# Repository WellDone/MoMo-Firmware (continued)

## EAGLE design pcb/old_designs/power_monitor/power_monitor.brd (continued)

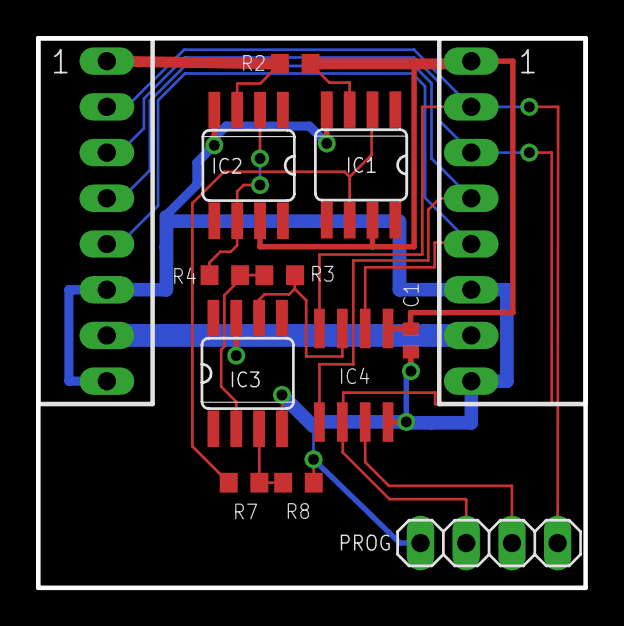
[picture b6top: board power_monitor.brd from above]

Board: 2 copper layers, 30.4 x 30.5 mm, 13 parts (0 on the bottom side), 14 nets.

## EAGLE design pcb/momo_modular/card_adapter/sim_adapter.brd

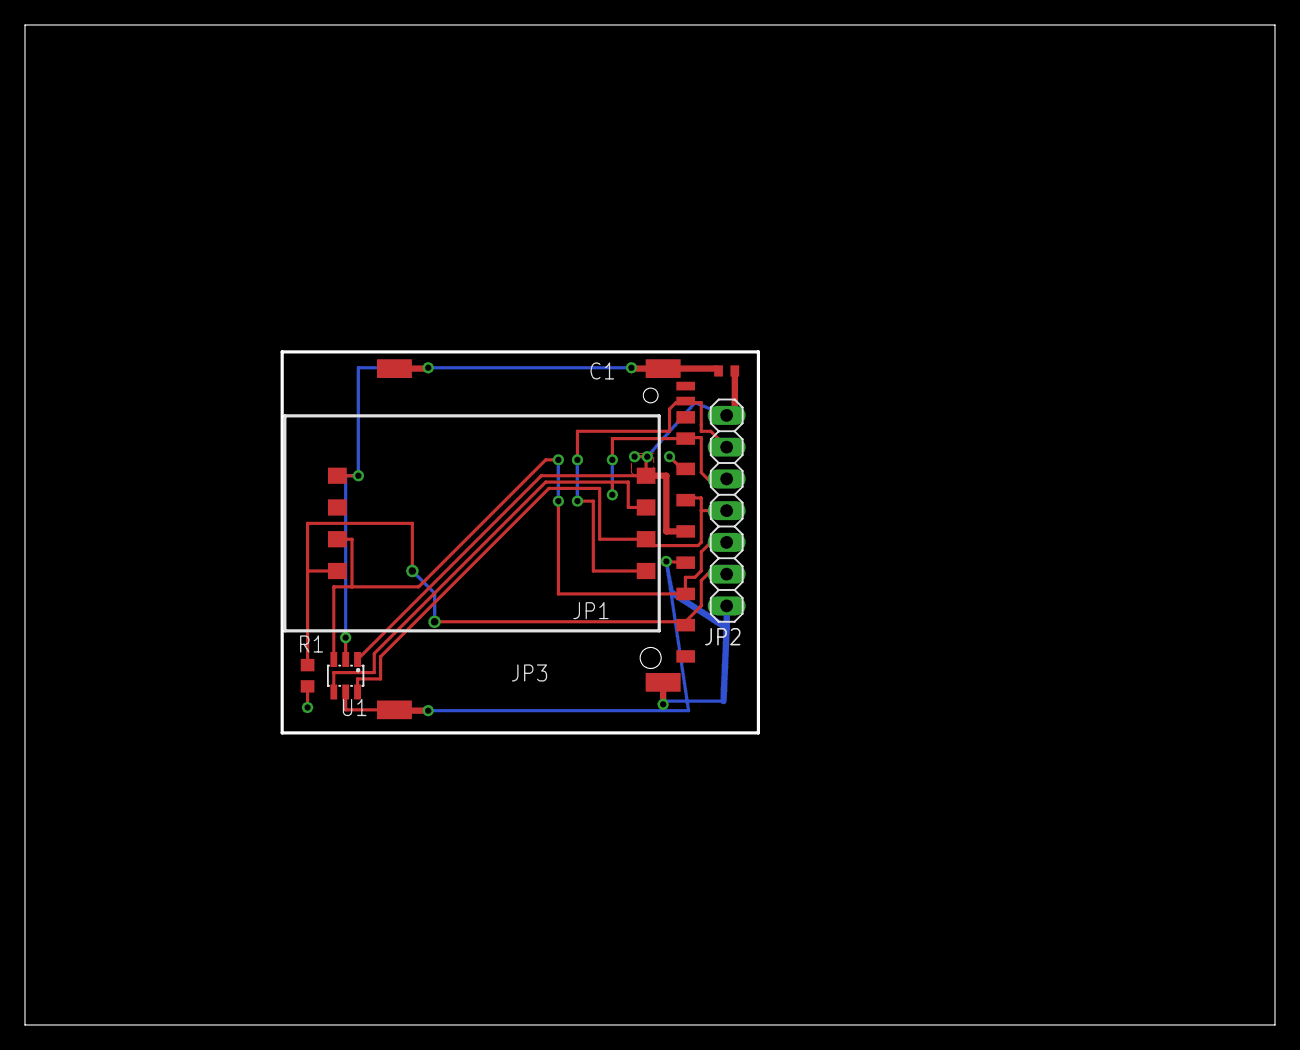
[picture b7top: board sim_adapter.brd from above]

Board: 2 copper layers, 99.7 x 79.7 mm, 6 parts (0 on the bottom side), 7 nets.

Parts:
C1: 100 nF; C0402
JP1: SIMHOLDER-8PINHING; CCM03-SIMHOLDER
JP2: 1X07
JP3: SDCARD-HOLDER; SDHOLDER-9PIN
R1: 10K; R0603
U1: ESDA6V1SC6; SOT23-6L

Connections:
GND: C1.2, JP1.GND, JP2.1, JP3.3, JP3.6, JP3.CDGND, JP3.CDGND_BOT, JP3.WPGND, JP3.WPGND_BOT, R1.2, U1.2, U1.5
IO1: JP1.SW2, JP2.2, JP3.1, R1.1
IO2: JP1.IO, JP2.3, JP3.2, U1.3
IO3: JP1.RESET, JP2.5, JP3.7, U1.4
IO4: JP1.CLOCK, JP2.4, JP3.5, U1.6
SENSE: JP1.SW1, JP2.6, JP3.CDETECT
VCC: C1.1, JP1.VCC, JP2.7, JP3.4, U1.1

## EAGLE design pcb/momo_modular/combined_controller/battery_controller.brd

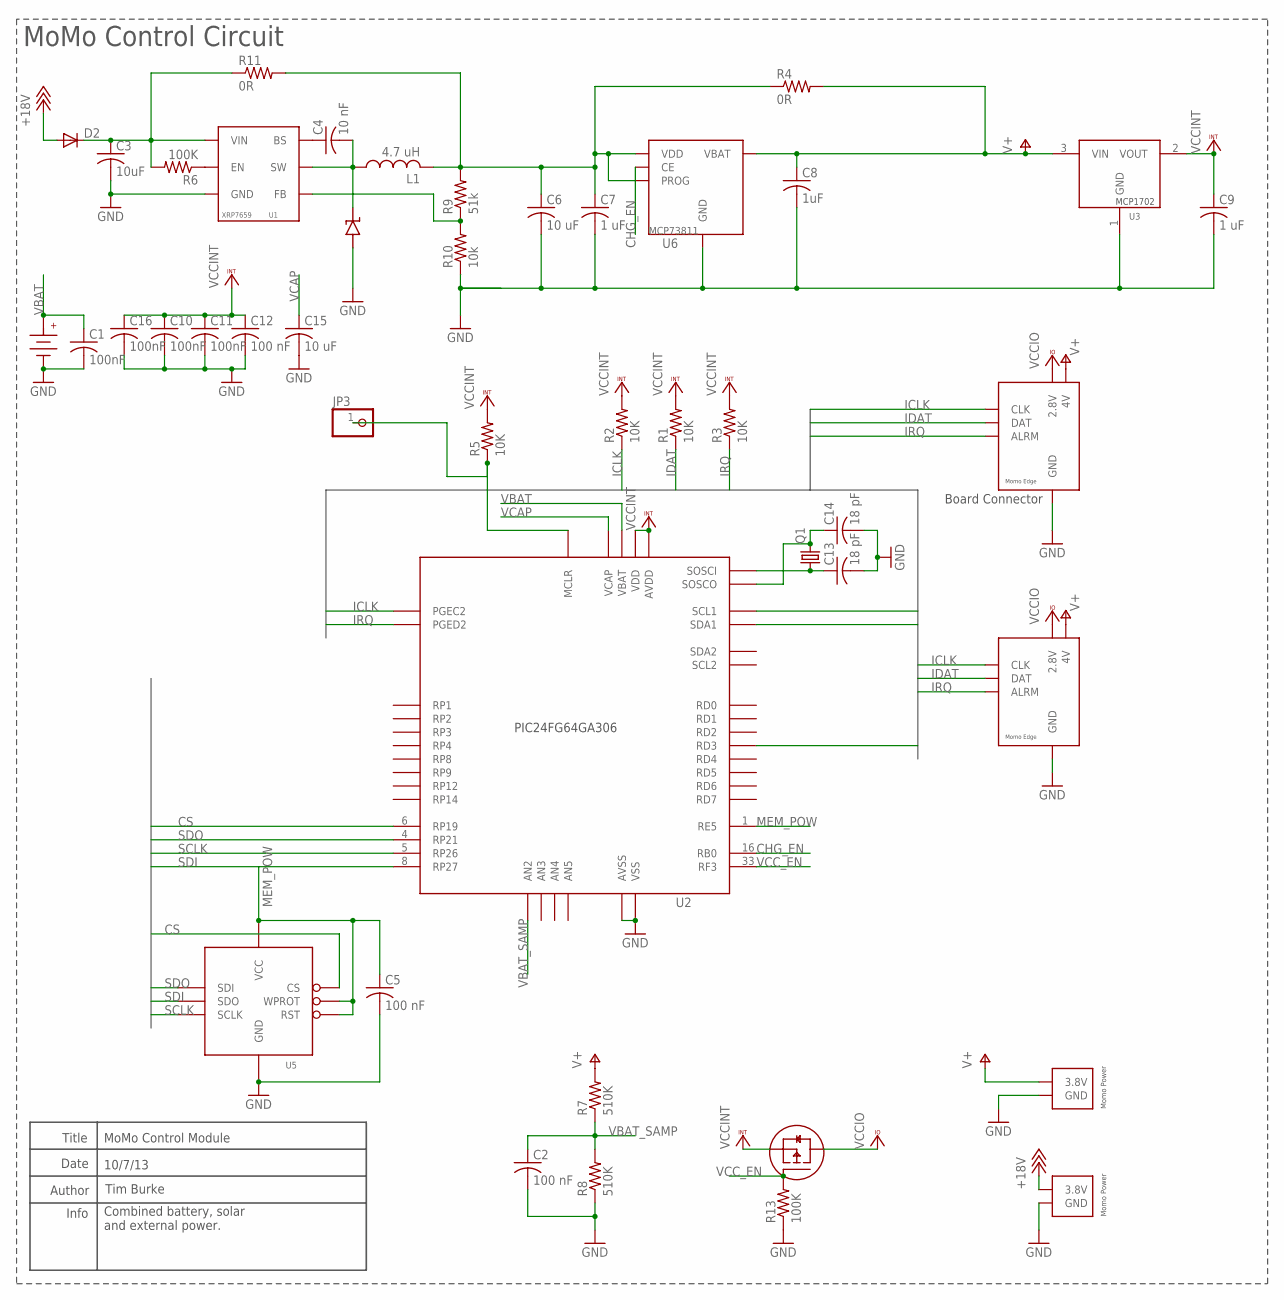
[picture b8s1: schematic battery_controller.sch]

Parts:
BATT1: CR1025-HOLDER
C1, C10, C11, C16: 100nF; C0402; DIGIKEY-PN 445-1265-1-ND
C2, C5, C12: 100 nF; C0402; DIGIKEY-PN 445-1265-1-ND
C3: 10uF; C0805; DIGIKEY-PN-BATT 587-2985-1-ND
C4: 10 nF; C0402; DIGIKEY-PN-BATT 445-1260-1-ND
C6: 10 uF; C0805; DIGIKEY-PN-BATT 587-2985-1-ND
C7: 1 uF; C0402; DIGIKEY-PN-BATT 445-4114-1-ND
C8: 1uF; C0402; DIGIKEY-PN-BATT 445-4114-1-ND
C9: 1 uF; C0402; DIGIKEY-PN 445-4114-1-ND
C13, C14: 18 pF; C0402K; DIGIKEY-PN 445-1238-1-ND
C15: 10 uF; C0805; DIGIKEY-PN 1276-1119-1-ND
D1: DIODE_SS2P3SS2P3; DIODE_SS2P3; DIGIKEY-PN-BATT SS2P3-M3/84AGICT-ND
D2: DIODE-DO214AC; DO214AC; DIGIKEY-PN SL13HE3/61TGICT-ND
JP1: MOMO-VERT-6M; 1X06; DIGIKEY-PN S1011EC-06-ND
JP2: MOMO-EDGE-6F; MOMO-EDGE-8F
JP3: PINHD-1X1; 1X01
JP4, JP5: MOMO-EDGE-POWER-M; MOMO-EDGE-SMALL-2M; DIGIKEY-PN A19450-ND
L1: 4.7 uH; NR6028-INDUCTOR; DIGIKEY-PN-BATT 587-2100-1-ND
Q1: CRYSTALTC26H; TC26H; DIGIKEY-PN 535-9034-ND
Q2: P-MOSFET; SOT23
R1, R2, R3, R5: 10K; R0603; DIGIKEY-PN P10.0KHCT-ND
R4: 0R; R0603; DIGIKEY-PN-EXTPOWER P0.0GCT-ND
R6: 100K; R0603; DIGIKEY-PN-BATT P100KHCT-ND
R7, R8: 510K; R0603; DIGIKEY-PN P510KHCT-ND
R9: 51k; R0603; DIGIKEY-PN-BATT P51.0KHCT-ND
R10: 10k; R0603; DIGIKEY-PN-BATT P10.0KHCT-ND
R11: 0R; R0603; DIGIKEY-PN-SOLAR P0.0GCT-ND
R13: 100K; R0603; DIGIKEY-PN P100KHCT-ND
U1: XRP7659; SOT23-6L; DIGIKEY-PN-BATT 1016-1751-1-ND
U2: PIC24FJ64GA306; TQFP64-10X10
U3: MCP1702; SOT23; DIGIKEY-PN MCP1702T-2802E/CBCT-ND
U5: FLASH8MSOP8; SOP08; DIGIKEY-PN M25PX80-VMN6TPCT-ND
U6: MCP73811; SOT23-5L; DIGIKEY-PN-BATT MCP73811T-420I/OTCT-ND

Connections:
+18V: D2.A, JP5.2 (3.8V)
BUCK_EN: R6.1, U1.4 (EN)
CHG_EN: U2.16 (RB0), U6.1 (CE)
CS: U2.6 (RP19), U5.1 (CS)
GND: BATT1.-1 (-), BATT1.-2 (-), C1.2, C2.2, C3.2, C5.2, C6.2, C7.2, C8.2, C9.2, C10.2, C11.2, C12.2, C13.2, C14.2, C15.2, C16.2, D1.AN, JP1.7 (GND), JP2.GND, JP4.1 (GND), JP5.1 (GND), R8.1, R10.1, R13.1, U1.2 (GND), U2.9 (VSS), U2.20 (AVSS), U2.25 (VSS), U2.41 (VSS), U3.1 (GND), U5.4 (GND), U6.2 (GND)
ICLK: JP1.3 (CLK), JP2.CLK, R2.1, U2.17 (PGEC2), U2.37 (SCL1)
IDAT: JP1.4 (DAT), JP2.DAT, R1.1, U2.36 (SDA1)
IRQ: JP1.5 (ALRM), JP2.ARLM (ALRM), R3.1, U2.18 (PGED2), U2.51 (RD3)
MEM_POW: C5.1, U2.1 (RE5), U5.3 (WPROT), U5.7 (RST), U5.8 (VCC)
unnamed: C3.1, D2.C, R6.2, R11.1, U1.5 (VIN)
unnamed: JP3.1, R5.1, U2.7 (MCLR)
unnamed: C6.1, C7.1, L1.2, R4.1, R9.2, R11.2, U6.4 (VDD), U6.5 (PROG)
unnamed: C14.1, Q1.2, U2.48 (SOSCO)
unnamed: C13.1, Q1.1, U2.47 (SOSCI)
unnamed: R9.1, R10.2, U1.3 (FB)
unnamed: C4.1, U1.1 (BS)
unnamed: C4.2, D1.CATH, L1.1, U1.6 (SW)
SCLK: U2.5 (RP26), U5.6 (SCLK)
SDI: U2.8 (RP27), U5.2 (SDO)
SDO: U2.4 (RP21), U5.5 (SDI)
V+: C8.1, JP1.6 (4V), JP2.V4 (4V), JP4.2 (3.8V), R4.2, R7.2, U3.3 (VIN), U6.3 (VBAT)
VBAT: BATT1.+, C1.1, U2.57 (VBAT)
VBAT_SAMP: C2.1, R7.1, R8.2, U2.14 (AN2)
VCAP: C15.1, U2.56 (VCAP)
VCCINT: C9.1, C10.1, C11.1, C12.1, C16.1, Q2.2 (SOURCE), R1.2, R2.2, R3.2, R5.2, U2.10 (VDD), U2.19 (AVDD), U2.26 (VDD), U2.38 (VDD), U3.2 (VOUT)
VCCIO: JP1.1 (2.8V), JP2.V28 (2.8V), Q2.3 (DRAIN)
VCC_EN: Q2.1 (GATE), R13.2, U2.33 (RF3)

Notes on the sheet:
Title
Author
Date
Tim Burke
Info
Board Connector
MoMo Control Module
10/7/13
MoMo Control Circuit
Combined battery, solar and external power.

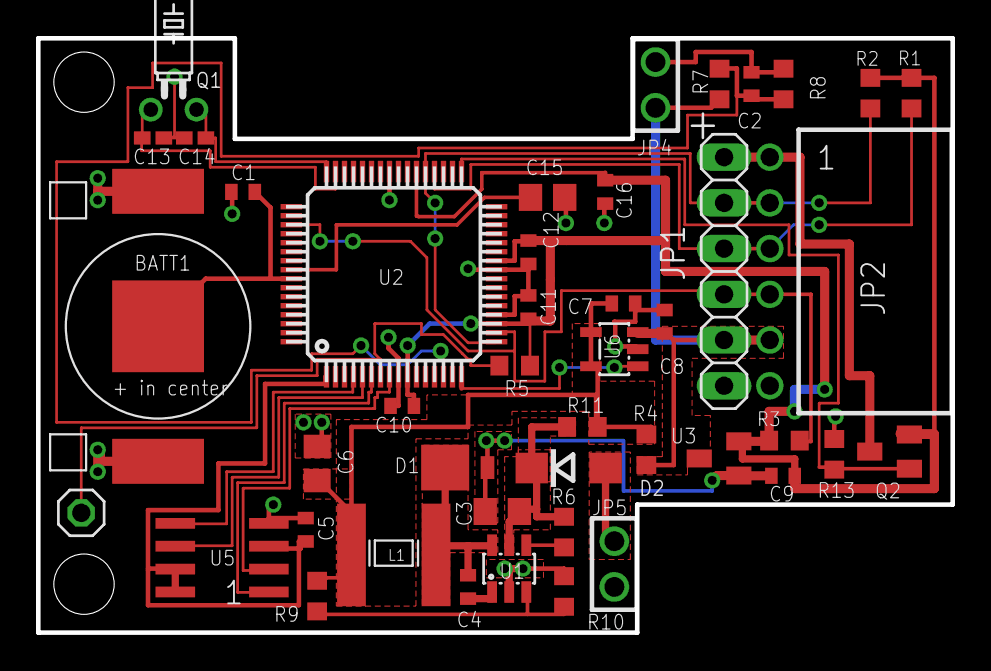
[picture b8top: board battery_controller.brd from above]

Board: 2 copper layers, 50.8 x 33.0 mm, 44 parts (0 on the bottom side), 27 nets.

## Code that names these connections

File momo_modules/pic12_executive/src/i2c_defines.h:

//i2c_defines.h
/*
 * All i2c constant values for sharing between c and asm code.
 */

#ifndef __i2c_defines_h__
#define __i2c_defines_h__

#ifdef __PIC16LF1823__
#define SDAPIN		RC1	
#define SCLPIN		RC0

#define I2CPORT		PORTC

#define SDATRIS		TRISC1
#define SCLTRIS		TRISC0
#define ALARM		A2
#define ALARMIOC	2
#define ALARMPORT	a
#define ALARMPORT_ASM A

#elif  __PIC12LF1822__
#define SDAPIN		RA2	
#define SCLPIN		RA1

#define I2CPORT		PORTA

#define SDATRIS		TRISA2
#define SCLTRIS		TRISA1
#define ALARM		A5
#define ALARMIOC	5
#define ALARMPORT	a
#define ALARMPORT_ASM A

#elif  __PIC16LF1847__
#define SDAPIN		RB1
#define SCLPIN		RB4

#define I2CPORT		PORTB

#define SDATRIS 	TRISB1
#define SCLTRIS		TRISB4
#define ALARM		B0
#define ALARMIOC	0
#define ALARMPORT 	b
#define ALARMPORT_ASM B
#else
#error Unsupported Platform, need to know i2c pin locations.
#endif

#define kI2CIdleState 				0
#define kI2CSendAddressState 		1
#define kI2CSendDataState 			2
#define kI2CReceiveDataState 		3
#define kI2CUserCallbackState 		4

#define kI2CStateMask				0b111
#define kI2CStatusMask				~(kI2cStateMask)
#define kI2CErrorMask				(0b11 << 6)

#define kI2CNoError 				(0 << 6)
#define kI2CInvalidChecksum 		(1 << 6)
#define kI2CNackReceived 			(2 << 6)
#define kI2CCollision 				(3 << 6)

#define kDisableI2CSlewControlFlag 	(1 << 7)
#define kSMBusLevelCompliantFlag 	(1 << 6)

#define kI2CFlagMask (kDisableI2CSlewControlFlag | kSMBusLevelCompliantFlag)

//both set CKP and SSPEN
#define kI2CMasterMode 				0b00111000            //set to master mode (0b1000)
#define kI2CSlaveMode 		        0b00110110            //set to slave mode (0b0110)


#endif

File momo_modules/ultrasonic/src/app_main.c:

//app_main.c

#include "platform.h"
#include "watchdog.h"
#include "port.h"
#include "mib12_api.h"
#include "watchdog.h"
#include "ioc.h"
#include "wpu.h"
#include "communication.h"
#include "tdc1000.h"
#include "tdc7200.h"
#include "measure.h"
#include "state.h"
#include "autoconf.h"
#include "automeasure.h"
#include <stdint.h>

//Global State
module_state	state;

static void copy_tof_to_mib(uint8_t tof_index, uint8_t mib_index);
static void process_async_actions();

extern int32_t 	delta_tof_accum;
extern uint16_t num_measurements;
extern int32_t last_automatic_reading;

void task(void)
{
	switch(state.mode)
	{
		case kManualMode:
		if (state.flags.value)
			process_async_actions();
		break;

		case kAutomaticMode:
		automatic_measurement();
		break;
	}
}

static void process_async_actions()
{
	if (state.flags.take_delta_tof_measurement)
	{
		UltrasoundError err;
		int32_t *mib = (int32_t *)mib_buffer;

		if (mib_buffer[2] == 0)
			err = accumulate_delta_tof(mib_buffer[0]);
		else
			err = fast_accumulate_delta_tof(mib_buffer[0]);

		mib[0] = delta_tof_accum;
		mib[1] = num_measurements;
		mib_buffer[8] = err;

		state.flags.take_delta_tof_measurement = 0;

		bus_master_async_callback(9);
	}


	if (state.flags.take_tof_measurement)
	{
		uint8_t direction = mib_buffer[0];

		enable_power();
		tdc7200_setaverages(0);
		tdc1000_prepare_deltatof(0);

		LATCH(CHSEL) = direction;
		
		take_measurement();
		tdc7200_readresults();

		copy_tof_to_mib(0, 0);
		copy_tof_to_mib(1, 4);
		copy_tof_to_mib(2, 8);
		copy_tof_to_mib(3, 12);
		mib_buffer[16] = tdc7200_readfast(kTDC7200_INTStatusReg);

		//copy_tof_to_mib(4, 16);

		state.flags.take_tof_measurement = 0;
		disable_power();

		bus_master_async_callback(17);
	}

	if (state.flags.find_signal_strength)
	{
		mib_buffer[0] = find_signal_strength();
		state.flags.find_signal_strength = 0;
		bus_master_async_callback(1);
	}

	if (state.flags.find_optimal_gain)
	{
		mib_buffer[5] = find_optimal_gain((int32_t *)&mib_buffer[0], &mib_buffer[4]);
		state.flags.find_optimal_gain = 0;
		bus_master_async_callback(6);
	}

	if (state.flags.find_pulse_variance)
	{
		find_pulse_variance((int32_t *)&mib_buffer[0]);
		state.flags.find_pulse_variance = 0;
		bus_master_async_callback(20);
	}
}

void interrupt service_isr()
{
	
}

void initialize(void)
{
	//Initialize all of our PINS to digital
	ENSURE_DIGITAL(CLOCKENABLE);
	ENSURE_DIGITAL(RESET1000);
	ENSURE_DIGITAL(ERR1000);
	ENSURE_DIGITAL(CHSEL);
	ENSURE_DIGITAL(INT7200);
	ENSURE_DIGITAL(ENABLE);
	ENSURE_DIGITAL(TRIG);
	ENSURE_DIGITAL(SDO);
	ENSURE_DIGITAL(SDI);
	ENSURE_DIGITAL(SCK);
	ENSURE_DIGITAL(CS7200);
	ENSURE_DIGITAL(CS1000);

	//Setup control pins correctly 
	//Enable and Clock Enable are active high to turn on the
	//clock and ultrasonic chips

	LATCH(CLOCKENABLE) = 0;
	PIN_DIR(CLOCKENABLE, OUTPUT);

	LATCH(ENABLE) = 0;
	PIN_DIR(ENABLE, OUTPUT);

	//Reset is active high
	LATCH(RESET1000) = 0;
	PIN_DIR(RESET1000, OUTPUT);

	enable_weak_pullups();

	//Trigger is a signal from TDC7200 to TDC1000
	PIN_DIR(TRIG, INPUT);

	//Interrupt is an open-drain signal from TDC7200 to MCU
	PIN_DIR(INT7200, INPUT);
	enable_pullup(INT7200);

	//Error is an open-drain signal from TDC1000 to MCU
	PIN_DIR(ERR1000, INPUT);
	enable_pullup(ERR1000);

	//Channel select is largely ignored in the measurement modes we use
	LATCH(CHSEL) = 0;
	PIN_DIR(CHSEL, OUTPUT);

	init_spi();
	tdc1000_init();
	tdc7200_init();

	initialize_parameters();

	tdc1000_setmode(kTDC1000_TOFMode);
	tdc1000_setexternal(1);

	last_automatic_reading = 0;

	state.flags.value = 0;
	state.mode = kAutomaticMode;
	state.autostatus = kNotInAutomaticMode;
}

void main(void)
{
	initialize();

	while(1)
	{
		task();
		asm("sleep");
	}
}

static void copy_tof_to_mib(uint8_t tof_index, uint8_t mib_index)
{
	int32_t tof = tdc7200_tof(tof_index, 0);

	mib_buffer[mib_index + 0] = (tof >> 0) & 0xFF;
	mib_buffer[mib_index + 1] = (tof >> 8) & 0xFF;
	mib_buffer[mib_index + 2] = (tof >> 16) & 0xFF;
	mib_buffer[mib_index + 3] = (tof >> 24) & 0xFF;
}

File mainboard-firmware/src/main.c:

#include <stdlib.h>
#include "common.h"
#include "reset_manager.h"
#include "task_manager.h"
#include "scheduler.h"
#include "bus_master.h"

// FBS
#pragma config BWRP = OFF               // Table Write Protect Boot (Boot segment may be written)
#pragma config BSS = OFF                // Boot segment Protect (No boot program Flash segment)

// FGS
#pragma config GWRP = OFF               // General Segment Code Flash Write Protection bit (General segment may be written)
#pragma config GCP = OFF                // General Segment Code Flash Code Protection bit (No protection)

// FOSCSEL
#pragma config FNOSC = FRCPLL           // Oscillator Select (8 MHz FRC oscillator (FRC)) with PLL
#pragma config IESO  = OFF              // Internal External Switch Over bit (Internal External Switchover mode disabled (Two-Speed Start-up disabled))

// FOSC
#pragma config POSCMOD = NONE           // Primary Oscillator Configuration bits (Primary oscillator disabled)
#pragma config OSCIOFNC = ON           // CLKO Enable Configuration bit (CLKO output signal is active on the OSCO pin)
#pragma config POSCFREQ = HS            // Primary Oscillator Frequency Range Configuration bits (Primary oscillator/external clock input frequency greater than 8 MHz)
#pragma config SOSCSEL = SOSCHP         // SOSC Power Selection Configuration bits (Secondary oscillator configured for high-power operation)
#pragma config FCKSM = CSECMD           // Clock Switching and Monitor Selection (Clock switching is enabled, Fail-Safe Clock Monitor is disabled)

// FWDT
#pragma config WDTPS = PS32768          // Watchdog Timer Postscale Select bits (1:32,768)
#pragma config FWPSA = PR128            // WDT Prescaler (WDT prescaler ratio of 1:128)
#pragma config WINDIS = OFF             // Windowed Watchdog Timer Disable bit (Standard WDT selected; windowed WDT disabled)
#pragma config FWDTEN = OFF             // Watchdog Timer Enable bit (WDT disabled (control is placed on the SWDTEN bit))

// FPOR
#pragma config BOREN = BOR0             // Brown-out Reset Enable bits (Brown-out Reset disabled in hardware; SBOREN bit disabled)
#pragma config PWRTEN = ON              // Power-up Timer Enable bit (PWRT enabled)
#pragma config I2C1SEL = PRI            // Alternate I2C1 Pin Mapping bit (Default location for SCL1/SDA1 pins)
#pragma config BORV = V18               // Brown-out Reset Voltage bits (Brown-out Reset set to lowest voltage (1.8V))
#pragma config MCLRE = ON               // MCLR Pin Enable bit (RA5 input pin disabled; MCLR enabled)

// FICD
#pragma config ICS = PGx1               // ICD Pin Placement Select bits (PGC1/PGD1 are used for programming and debugging the device)

// FDS
#pragma config DSWDTPS = DSWDTPSF       // Deep Sleep Watchdog Timer Postscale Select bits (1:2,147,483,648 (25.7 Days))
#pragma config DSWDTOSC = LPRC          // DSWDT Reference Clock Select bit (DSWDT uses LPRC as reference clock)
#pragma config RTCOSC = LPRC            // RTCC Reference Clock Select bit (RTCC uses LPRC as reference clock)
#pragma config DSBOREN = ON             // Deep Sleep Zero-Power BOR Enable bit (Deep Sleep BOR enabled in Deep Sleep)
#pragma config DSWDTEN = OFF            // Deep Sleep Watchdog Timer Enable bit (DSWDT disabled)

void blink_light1(void)
{
	_RA0 = !_RA0;
}

void send_erase_message(void)
{
    bus_master_rpc(NULL, 8, 255, 0x00, NULL, 0);
}

void send_write_message(void)
{
    MIBIntParameter param1;       
    MIBIntParameter param2;
    MIBBufferParameter param3;
    char *msg = "test";

    MIBParameterHeader *params[3];

    params[0] = (MIBParameterHeader*)&param1;
    params[1] = (MIBParameterHeader*)&param2;
    params[2] = (MIBParameterHeader*)&param3;

    bus_init_int_param(&param1, 0);
    bus_init_int_param(&param2, 1<<12);
    bus_init_buffer_param(&param3, msg, 5);

    bus_master_rpc(NULL, 8, 255, 0x01, params, 3);
}

void send_read_message(void)
{
    MIBIntParameter param1;       
    MIBIntParameter param2;
    MIBIntParameter param3;

    MIBParameterHeader *params[3];

    params[0] = (MIBParameterHeader*)&param1;
    params[1] = (MIBParameterHeader*)&param2;
    params[2] = (MIBParameterHeader*)&param3;

    bus_init_int_param(&param1, 0);
    bus_init_int_param(&param2, 1<<12);
    bus_init_int_param(&param3, 5);

    bus_master_rpc(NULL, 8, 255, 0x02, params, 3);
}

void send_test_message(void)
{
    static unsigned int i = 0;

    if (i == 0)
        send_erase_message();
    else if(i==1)
        send_write_message();
    else if(i==2)
        send_read_message();

    ++i;

    if (i == 3)
        i = 0;
}

void send_blink_message(void)
{
    MIBIntParameter param1;
    MIBIntParameter param2;
    MIBParameterHeader *params[2];

    params[0] = (MIBParameterHeader*)&param1;
    params[1] = (MIBParameterHeader*)&param2;

    bus_init_int_param(&param1, 5);
    bus_init_int_param(&param2, 6);
    bus_master_rpc(NULL, 8, 0x02, 0x01, params, 2);
}

ScheduledTask task1;
ScheduledTask i2c;

int main(void) 
{
    AD1PCFG = 0xFFFF;

    _TRISA1 = 0;
    _TRISA0 = 0;
    _TRISA6 = 0;

    _RA1 = 1;
    _RA0 = 1;
    _RA6 = 1;

    handle_reset();

    scheduler_schedule_task(blink_light1, kEverySecond, kScheduleForever, &task1);
    //scheduler_schedule_task(send_test_message, kEverySecond, kScheduleForever, &i2c);

    taskloop_loop();

    return (EXIT_SUCCESS);
}

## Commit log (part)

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2014-06-08 Initial microsim pad layout for checking against 3d model
2014-06-09 Update version numbers
2014-06-09 Update part descriptions for automatic BOM generation
2014-06-09 Revise GSM module to include pic16lf1847, microsim
    Also updated layout for better reflow and moved
    traces further from board edges.
2014-06-10 Fix code path that would disable interrupts for 16000 cycles
    No indication that this was actively causing a bug but it could cause
    issues.
2014-06-14 Add 10 us low alarm pulse resets all slaves.
    - Reimplement bus slave logic in assembly for optimized size
    - Changed several functions to indicate return value using status
    bits like ZERO for optimized checks.
    - Implemented bus_slave_callhandler in assembly
2014-06-14 Properly clear IOC flag after checking
2014-06-14 Increase pic12_executive serial number to reflect IOC addition
2014-06-14 Add label text for new controller version.
2014-06-17 Implement reset delay to allow modules to reset themselves
    Adds a 100 ms wait from the time ALARM is asserted to the time the
    bus power goes off to allow chips to reset and clear all of their
    pins. This disables any additional circuitry on the bus that may
    be power the bus parasitically when main power is cut and prevent
    a proper reset sequence.
2014-06-21 Redo timestamp generation to be more efficient
    New implementation uses logarithmic lookup tables to avoid any
    32 bit multiplications. Implementation complexity is log(N) in the
    number of bits required to represent the datetime and only uses
    32 bit addition with a few small lookup tables.
2014-06-23 Reimplement construct report to avoid pointer math
2014-06-24 Add lightweight performance counter module
    Module configures a freerunning 32-bit timer running at the same
    frequency as the CPU instructions. An arbitray number of perormance
    counters can be configured to micro-profile individual regions of code.
    Calling PROFILE_START(counter_id) captures the current timer value.
    Calling PROFILE_END(counter_id) stores the elapsed time since the
    last call to PROFILE_START with the counter id. The times can be
2014-06-24 Add support for new report format in reportinator tool
    - Uses uint32 timestamps rather than 6-byte datetime codes
2014-06-24 Add support for perf counters and reading ram
    - also drive bus voltage transistor rather than just letting it
    get pulled up to VCC to make it more robust against noise. I do
    not believe that this caused a problem before but it's better to
    drive signals than to let them be pulled up by high value resistors
2014-06-26 Fix interval calculation bug in construct_report
    construct_report function should now be safe and working. Command
    line testing shows it to function correctly. It can process about
    300 events per second, so large event queues will still be slow.
    Major slowdown now seems to be in reading the sensor events in from
    flash. This is currently done 1 at a time so increasing the read
    buffer will probably help.
2014-06-29 Update momo tool to include a shell and print better help
    If you pass a command line to momo that ends not with data but with
    a context object, you will be presented with a shell that starts
    with that context. The help system now presents much better help
    documentation as well, pulled from the context and function docstrings
2014-07-04 Update momo tool to allow for parallel builds
    You cannot run scons via the import command in python. For whatever
    reason, it causes the command to hang when you do a parallel build
    with -jN. Running via a simple function wall works.
2014-07-06 Change asyncio to be line oriented with a configuratable separator string
2014-07-09 Remove extraneous file.
2014-07-09 Fix flash_queue_walker initialization in read_report_log.
2014-07-09 Fix broken include.
2014-07-10 Add ability to run programs, wait for them and parse errors to SIM30
2014-07-20 Fix provisioning script to properly use cached SCONS installer.
2014-07-21 Reduce sampling rate to every 10 seconds, don't truncate counter data at 8 bits, measure flow rate once rather than trying to explicitly integrate over the course of an entire event.
2014-07-21 Fix some issues with report retry beavior, support reading report log from the command line.
2014-07-21 Don't report error details (to save ROM on the GSM pic)
2014-07-21 Add an 'abandon stream' endpoint to gsm_module.
2014-07-21 Limit retry repetition.
2014-07-22 Report error messages again and fix the param spec for the failure notification MIB endpoint.
2014-07-22 Comment to de-mystify the magic timestamp offset number.
2014-08-04 Fix module iterator to not go past the end of attached modules
2014-08-04 Do not remove tasks that are not scheduled.
2014-08-13 Fix integer overflow error causing truncated reports
2014-08-24 Rewrite ChipFamily and ChipSettings to be more general
    New build system allows for an arbitrary number of architectures
    to be specified for each module. Architectures can override definitions
    from archs earlier in the list and modules can define overlays for
    each architecture. A chip is just a specific architecture. This will
    allow for more easy expansion to building unit tests on pic24 since
    you will be able to add the test architecture on top of all other
2014-08-24 Finish updating build_settings.json for compat with new build system
2014-08-25 Update pymomo unit tests for latest build system changes
2014-08-26 Add patch for latest svn HEAD of gpsim to fix it.
    There are errors in the current head of gpsim that prevent it from
    correctly simulating Enhanced Midrange PICs in certain subtle ways
    that break unit tests for MoMo. This patch applies cleanly to
    gpsim svn HEAD and fixes the issues. A bug report has been submitted
    with the patch so hopefully this will be fixed upstream in the future.
2014-08-31 Fix quoting bug with spaces in path
2014-09-01 Change error type for consistency
2014-09-21 Update unity to work with PIC24FJ64GA306 and PIC24F16KA101
2014-09-25 Start adding support for running unit tests
2014-09-25 Update linkedlist test to work with new unit testing framework
2014-09-29 Update SConstruct files to include local module settings
2014-09-30 Update to not pull in pic24 feature definitions
    This is never referenced in the PIC12 executive code, but xc8 does
    not seem capable of optimizing it out (but only on 16lf1847) so it
    causes problems with the memory layout.
2014-10-01 Reference the correct TravisCI instance in README (note: this will refect the build status of the most recent change, regardless of branch) and add a placeholder for a future pic12_executive build
2014-10-06 Use a local copy of flatdocs, modified to serve multiple pages of markdown.
2014-10-11 Don't open a shell when a command-line execution fails. Only open a shell when "-i" or "--interactive" is specified as the first argument to the momo command.
2014-10-12 Serve the new markdown documentation files on the github pages site.
2014-10-16 If one of the build steps fails, fail the entire build.
2014-10-16 Rename 02-modules.md to 10-modules.md
2014-10-17 Create 18-Support-Modules
2014-10-17 Rename 18-Support-Modules to 18-Support-Modules.md
2014-10-25 Update pcb build system and bugfixes
    - support finding eagle via path
    - support automatic creation of Diode Descriptions
    Update controller board to rev 4.0.
    - New version contains BTLE via Microchip RN4020 module
    - Voltage supervisor with hard reset capability from bluetooth
    or via microcontroller
2014-10-31 add export in front of four PATHs
2014-11-02 Remove old cruft from README
    The link to the documentation page should be enough
2014-11-15 Refactor out code for dealing with cmdline simulators
    Start integrating gpsim into simulator framework
    Start adding gpsim functionality
    Update support for gpsim
    Update gpsim support to include loading, logging and parsing errors
    Update pic12_executive unit tests to support 16lf1847
    - modify bus_slave test to use correct pin for i2c comms
2014-11-19 Master i2c routines now send correct packets
    - i2c checksum calculation works
    - master routines properly acks and nacks packets
    - no more off-by-one error calculating packet lengths
    - removed unnecessary C files
2014-11-26 Update mainboard with first version of btle code
2014-11-28 Add bootloader checking feature to modtool to diagnose bootloader issues.
2014-12-08 Update battery to handle logic for controlling charging
2015-01-05 Update momo shell with better help features and ability to add packages
    - You can now add a package and have it show up as a context in momo
    - Functions are now listed with short descriptions
    - Various bugs dealing with handling contexts are fixed
    Update pymomo unit tests for compatibility with API.
    Update syslog and add unit tests
    Add LDF compiler and add header dependency tracking to xc16 build system
2015-01-10 First version that compiles.
2015-01-11 Update shared pic12 code with bug fixes
2015-01-14 Address issues with multisensor code
2015-01-22 Remove the global momo executable scripts from MoMo-Firmware - they are now packaged with PyMoMo.
2015-01-27 Add ability to build shared library without uart interrupts.
    Add ability to build shared library without uart interrupts.
    Update mainboard with first version of btle code
    Update library port module and add timer module.
    Update bootloader to support new controller version.
    Allow for easy modification of pin assignments and demonstrate btle
    Bugfix build system and update rn4020 to advertise itself.
2015-01-28 Update the report route MIB endpoints to work with longer route buffers.
2015-01-31 Fix initialization order for syslog
2015-02-01 Move gsm rx into assembly
2015-02-02 Fix handling of repeated characters in expect
2015-02-02 Update linear address space to not conflict with other variables
2015-02-03 Update tests and bugfixes
2015-02-04 Diagnoze and work around the most terrible XC8 compiler bug in the whole world. Also detect GSM band and attempt to optimistically select it for subsequent registrations.
2015-02-10 Better command trailing character handling and first-class capture_remainder support.
2015-02-10 Support HTTPS and fix stream precedence module reset behavior.
2015-03-14 Upgrade to xc8 v1.34 and xc16 v1.24.
2015-03-18 Add new mib slave responders and fix i2c checksum verification
2015-03-18 Allow for conditional overrides to support more rigorous pymomo CI testing.
2015-03-19 Update gpsim patch
2015-03-31 Add checksum restarting and more test cases to test_bus_master
2015-04-01 Add 16 ms timeout for collision recovery.
2015-04-07 Add first master module
2015-04-12 Update build scripts to print symbol table
2015-04-15 Update documentation for new mib block structure
2015-04-24 Check bus master functionality and checksum recovery.
2015-05-04 Update protocol defines
2015-05-06 Finish layout of ultrasonic board
2015-05-12 Working pic12 asynchronous mib calls and unit test coverage
2015-05-13 Bugfix for app verification
2015-05-14 Fix compilation on windows
2015-05-15 Start rewriting PIC24 mib code
2015-05-17 Update feature command ordering to preserve compatibility on the wire
2015-05-18 Update bus_is_idle to just check for a fixed period of time
2015-05-18 Reorder status bitfield for compatibility
2015-05-19 Update i2c captures with new byte ordering
2015-05-19 Update API with async callback
2015-05-19 Fix async implementation on pic24.
2015-05-21 Ultrasonic firmware first version
2015-05-29 Level and TOF measurements for ultrasound board
2015-05-29 Update multisensor to not use custom startup
2015-06-03 Update ultrasound
2015-06-16 Update code for compatibility with new pic12 executive
2015-06-30 Update MLDP support
2015-07-06 Branch to use script
2015-07-13 Update FSU for new momo api
2015-07-13 Fix timing issue sending commands to tdc7200
2015-07-22 Port gsm_module to new pic12_executive with asynchronous rpcs
    - async rpcs are implemented and tested for every command except
    the stream commands
2015-07-22 Working gsm firmware updated to new pic12_executive
    - asynchronous open and close stream commands
    - tested http, https and msg sending
2015-07-25 Update http and streaming methods for more error codes
2015-07-29 Updated mainboard code
2015-07-30 Update fsu to latest rpc queue format
